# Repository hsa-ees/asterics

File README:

,=============================================================================,
|                                                                             |
|                         The ASTERICS Framework                              |
|                                                                             |
'============================================================================='

Authors: Michael Schaeferling <michael.schaeferling@hs-augsburg.de>
         Gundolf Kiefer <gundolf.kiefer@hs-augsburg.de>

Date:    2019-09-16

Getting Started
===============

To get a fast introduction on how to use the ASTERICS framework, 
we advise you to take a look at the ASTERICS manual.

Chapter 2 "Using ASTERICS" gives information on 
 * how to setup ASTERICS (2.1) and
 * how to get startet with the reference demo design (2.2).

The manual and a snapshot of the ASTERICS framework are available at:

  http://ees.hs-augsburg.de/asterics

Licensing and Additonal Modules
===============================

This document and the mentioned download link refer to the free and publicly
available part of ASTERICS. This part is generally licensed under the LPGL
(see LICENSE for details).

However, there are more ASTERICS modules available, which are presently not
published under an open source license, but that can be made available
individually on a per-project basis. These include modules for:

* the Generalized Hough Transform and other variants of the Hough Transform
  [1, 2]

* low latency lense distortion removal and stereo rectification (NITRA) [4, 5]

* efficient, on-the-fly point feature extraction (SURF algorithm) [3]

Please contact the Efficient Embedded Systems (EES) group at the University of
Applied Sciences Augsburg (see "authors" section on top of the file) for
further information on using these modules and collaborating with the EES group.

Acknowledgments
===============

Parts of this work have been supported by the German Federal Ministry for
Economic Affairs and Energy (BMWi), grant number ZF4102001KM5 (2015-2018).

Parts of this work have been supported by the German Federal Ministry of
Education and Research (BMBF), grant number 17N3709 (2009-2013).

References
==========

[1] Julian Sarcher, Christian Scheglmann, Alexander Zoellner, Tim Dolereit,
    Michael Schaeferling, Matthias Vahl, Gundolf Kiefer: "A Configurable
    Framework for Hough-Transform-Based Embedded Object Recognition Systems",
    IEEE International Conference on Application-specific Systems, Architectures
    and Processors (ASAP) 2018, Mailand, 10. Juli 2018
    
[2] Gundolf Kiefer, Matthias Vahl, Julian Sarcher, Michael Schäferling: "A
    Configurable Architecture for the Generalized Hough Transform Applied to the
    Analysis of Huge Aerial Images and to Traffic Sign Detection",
    IEEE International Conference on ReConFigurable Computing and FPGAs
    (ReConFig), 2016, DOI: 10.1109/ReConFig.2016.7857143.

[3] Matthias Pohl, Michael Schäferling, Gundolf Kiefer: "An Efficient FPGA-based
    Hardware Framework for Natural Feature Extraction and Related Computer
    Vision Tasks", 24th International Conference on Field Programmable Logic and
    Applications (FPL), 2014, DOI: 10.1109/FPL.2014.6927463

[4] Matthias Pohl, Michael Schäferling, Gundolf Kiefer, Plamen Petrow, Egmont
    Woitzel, Frank Papenfuß: "Leveraging polynomial approximation for non-linear
    image transformations in real time", Computers & Electrical Engineering,
    Available online 23 January 2014, ISSN 0045-7906,
    DOI: 10.1016/j.compeleceng.2013.12.011
    
[5] Matthias Pohl, Michael Schäferling, Gundolf Kiefer, Plamen Petrow, Egmont
    Woitzel, Frank Papenfuß: "An Efficient and Scalable Architecture for
    Real-Time Distortion Removal and Rectification of Live Camera Images",
    IEEE International Conference on ReConFigurable Computing and FPGAs
    (ReConFig), 2012, DOI: 10.1109/ReConFig.2012.6416730.

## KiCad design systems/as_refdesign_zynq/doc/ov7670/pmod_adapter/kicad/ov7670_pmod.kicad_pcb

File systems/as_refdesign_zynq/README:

,===========================================,
  |                                           |
  |  ASTERICS Framework Demonstration System  |
  |                                           |
  '==========================================='

Author: Michael Schaeferling <michael.schaeferling@hs-augsburg.de>
Date of revision: 2019-07-16

System Name: as_refdesign_zynq

Development environment: Xilinx Vivado 2017.2

Target Boards: 
  * Digilent ZYBO board (Zynq Z-7010, XC7Z010)

  Note: Vivado Board Files must be installed!
   Ensure you have installed the Vivado Board Files for your target
   board. These files can be obtained from Digilent or Avnet (they call 
   it "Board Definitions") and are placed in the Vivado installation
   directory at '%Vivado-Dir/data/boards/board_files/'.

Additional hardware required:
  * OmniVision OV7670 image sensor, connected to Pmods JB and JC (Zybo)
     -> use a "OV7670-Pmod Adapter v0.3" board for connection 
        (see 'doc/' for information on the adapter board)
  * a monitor, connected to the HDMI port (Zybo)

Info on Vivado IP cores:
  * ASTERICS: image data capture, processing and writing data to memory
  * VEARS: for visualization (part of the ASTERICS framework)

Software / demo system usage:
  The demo software is located at 'software/'. See the ASTERICS 
  reference software (should be part of the ASTERICS refernce design, 
  located at 'asterics/') for further details.

**************
* Quickstart *
**************
  0) For proper operation of Vivado (needed to generate an ASTERICS IP 
     core for Vivado and to build the system) make sure you source your 
     Vivado environment:
     > source <VIVADO-DIR>/settings64.sh
     
     Make sure you source the ASTERICS environment prior to any action 
     in the project folder:
     > source <ASTERICS-DIR>/settings.sh

  1) Change to your project folder and build the ASTERICS IP core for 
     use with Vivado (which will be integrated in the system):
     > make asterics_vivado_cores

  2) Build the whole system (hardware platform and demo software).
     This step will take some minutes:
     > make build_system

  3) Connect your Zybo with a monitor (HDMI port) and connect to your 
     computer. Also power on the board.
     Then upload the hardware and software to the board:
     > make run
     For usage instructions of the demo software please refer to the 
     README of the recent ASTERICS design.

****************
* Make Targets *
****************

  Following make targets help to use ASTERICS, either to use it to
  generate a vendor independent core or to build a complete system
  which is put to operation on the target board.

  * asterics_core :         Generate a general ASTERICS core
                            using "as_automatics", without the need for
                            vendor tools (e.g. Vivado) or a board.
                            Useful for vendor-indepenent evaluation of
                            the ASTERICS framework / generator,
                            but not needed for the system generation
                            and board operation (for this, we use the
                            target 'asterics_vivado_cores' instead).

  * asterics_vivado_cores : Generate the ASTERICS IP core for
                            Xilinx Vivado using "as_automatics"
                            and populate the software reference
                            implementation.

  * build_system:           Generate and build the whole demo system
                            (hardware + software) from sources.
                      NOTE: run target 'asterics_vivado_cores' before!

  * run:                    Run the demo on the target board.
                      NOTE: run target 'build_system' before!

  * all / build_and_run :   The lazy target: performs all needed steps
                            automatically, no more interaction needed.
                            This one uses following targets:
                              1) asterics_vivado_cores
                              2) build_system
                              3) run
                            Just make sure to connect the board, as it
                            will be programmed right after hardware and
                            software are built.

Directory structure:
 - as_refdesign_zynq/
   |- README:         This file.
   |- doc/:           additional documentation
   |- Makefile:       The main Makefile to build and run the system
   |- asterics/:      ASTERICS (reference) designs. Each design should 
   |                  contain a hardware definition and a suitable demo 
   |                  software.
   |- hardware/
   |  |- boards/:     board support files (blockdesign, constraints, ...)
   |  |- build/:      build directory, system level (generated)
   |  '- build.bd/:   build directory for blockdesign files (generated)
   |- software/:      Demo software for ASTERICS image processing
   |- vivado_cores/:  ASTERICS IP core repository, containing the
   |                  ASTERICS IP cores for use in Vivado (generated)
   '- asterics_core/: ASTERICS core (generated; Vivado is not needed to 
                      build this)

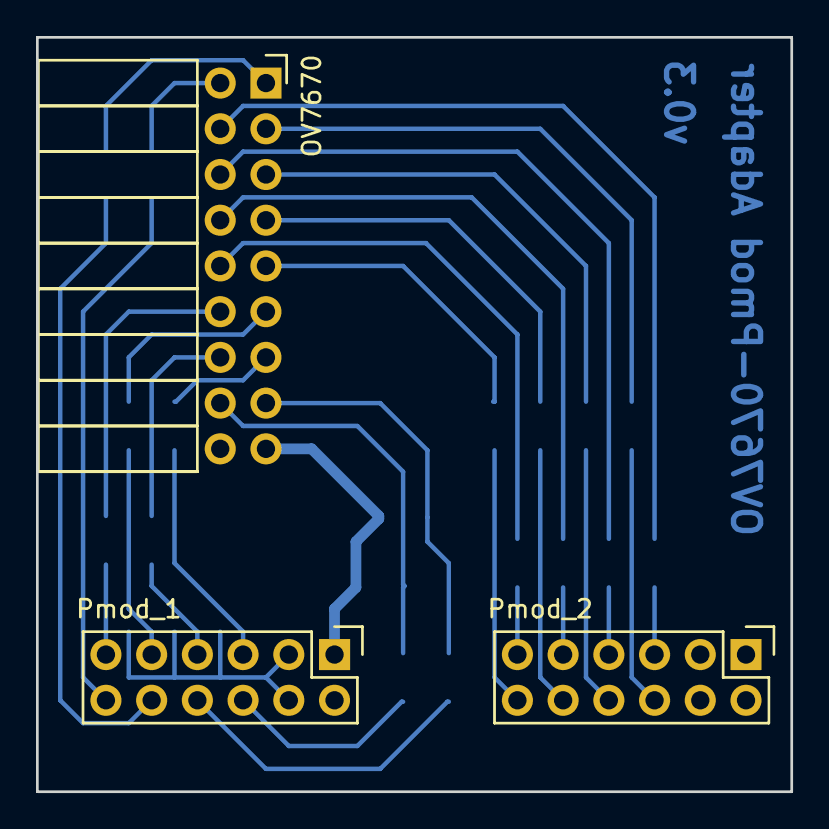
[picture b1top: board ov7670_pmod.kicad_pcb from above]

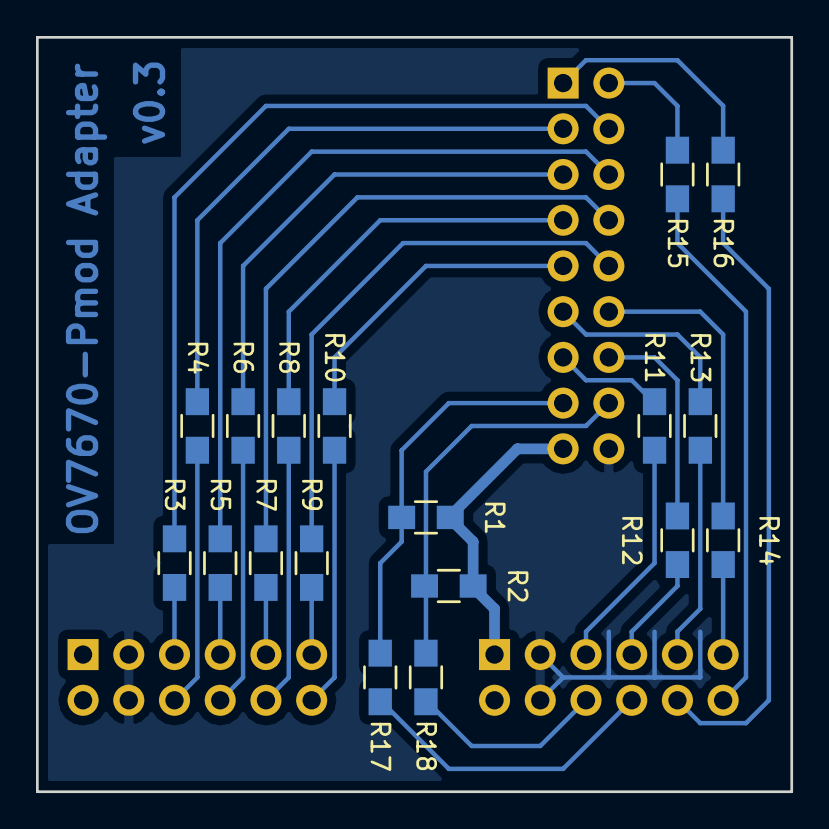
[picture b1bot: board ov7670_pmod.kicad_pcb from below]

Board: 2 copper layers, 41.9 x 41.9 mm, 21 parts (18 on the bottom side), 34 nets.

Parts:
OV7670: CONN_02X09; Socket_Strip_Angled_2x09
Pmod_1, Pmod_2: CONN_02X06; Pin_Header_Straight_2x06
R1, R2: 1k5; R_0805_HandSoldering
R3, R4, R5, R6, R7, R8, R9, R10, R11, R12, R13, R14, R15, R16, R17, R18: 100; R_0805_HandSoldering

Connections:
/D0: Pmod_2.5, R3.2
/D0_r: OV7670.4, R3.1
/D1: Pmod_2.6, R4.2
/D1_r: OV7670.3, R4.1
/D2: Pmod_2.7, R5.2
/D2_r: OV7670.6, R5.1
/D3: Pmod_2.8, R6.2
/D3_r: OV7670.5, R6.1
/D4: Pmod_2.9, R7.2
/D4_r: OV7670.8, R7.1
/D5: Pmod_2.10, R8.2
/D5_r: OV7670.7, R8.1
/D6: Pmod_2.11, R9.2
/D6_r: OV7670.10, R9.1
/D7: Pmod_2.12, R10.2
/D7_r: OV7670.9, R10.1
/GND: OV7670.18, Pmod_1.3, Pmod_1.4, Pmod_2.3, Pmod_2.4
/HREF: Pmod_1.7, R12.2
/HREF_r: OV7670.14, R12.1
/PCLK: Pmod_1.9, R13.2
/PCLK_r: OV7670.11, R13.1
/PWDN: Pmod_1.12, R15.2
/PWDN_r: OV7670.2, R15.1
/RESET: Pmod_1.10, R16.2
/RESET_r: OV7670.1, R16.1
/SIOC: Pmod_1.8, R17.2
/SIOC_r: OV7670.15, R1.2, R17.1
/SIOD: Pmod_1.6, R18.2
/SIOD_r: OV7670.16, R2.2, R18.1
/VSYNC: Pmod_1.5, R11.2
/VSYNC_r: OV7670.13, R11.1
/XCLK: Pmod_1.11, R14.2
/XCLK_r: OV7670.12, R14.1
VCC: OV7670.17, Pmod_1.1, Pmod_1.2, Pmod_2.1, Pmod_2.2, R1.1, R2.1

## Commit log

2020-02-13 README.md: Add "coming soon"
2020-09-28 Add main Makefile.
2021-03-15 Squashing merge from develop @17a52b23d17 to master for release 2021-03-15: Add (WIP) ASTERICS GUI; Automatics 2D Window Pipeline and CNN accellerator capabilities; Doxygen documentation; Major updat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
2021-03-15 Remove obsolete files overlooked in prior merge
2021-03-22 Add files required to create Linux devices, removed by prior commit
